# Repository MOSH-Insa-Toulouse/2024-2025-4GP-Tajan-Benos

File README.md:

# 2024-2025-4GP-Tajan-Benos

## SOMMAIRE
*** 
  - [I. Description Projet Graphite](#description-projet-graphite)
  - [II. Livrables](#livrables)
  - [III. Matériel nécessaire](#matériel-nécessaire)
  - [IV. Electronique Analogique sous LTSpice](#electronique-analogique-sous-ltspice)
  - [V. Création du PCB sous KiCad](#creation-du-pcb-sous-kicad)
  - [VI. Réalisation du shield](#réalisation-du-shield)
  - [VII. Code Arduino](#code-arduino)
  - [VIII. Application Android](#application-android)
  - [IX. Banc de test](#banc-de-test)
  - [X. Datasheet](#datasheet)
  - [XI. Conclusion](#conclusion)

*** 

## Description Projet Graphite

&nbsp;&nbsp;&nbsp;&nbsp;&nbsp;&nbsp; Dans le cadre de l’UE "Du capteur au banc de test" en 4e année de Génie Physique à l’INSA Toulouse, nous avons développé un capteur de contrainte basé sur une technologie low-tech. Ce capteur utilise du graphite déposé sur une feuille de papier à l’aide d’un crayon. Lorsqu’on applique une déformation au papier, la structure du graphite change, ce qui modifie ses propriétés électriques, comme la résistance. Ce capteur low-tech fonctionne grâce à la variation des connexions conductrices entre les nano-particules de graphite. Le transport des électrons se fait par effet tunnel entre les particules. Lorsqu'une déformation est appliquée, la distance entre les atomes varie. En extension, certains chemins de conduction sont interrompus, augmentant la résistance. En compression, la distance diminue, créant de nouveaux chemins et réduisant la résistance. La jauge de contrainte mesure ces variations de résistance pour déterminer la déformation et la contrainte appliquées. \
&nbsp;&nbsp;&nbsp;&nbsp;&nbsp;&nbsp; Le projet a consisté à développer un système complet autour de ce capteur : modélisation d'électronique analogique, création d’un circuit imprimé (PCB), programmation avec Arduino, ajout d’une interface utilisateur (écran OLED, encodeur, etc.) et communication sans fil via Bluetooth pour une application mobile. Un banc de test a été réalisé pour évaluer les performances du capteur à l'aide d'un banc de mesure réalisé en 3D. L’ensemble du travail a abouti à la rédaction d’une datasheet, décrivant les caractéristiques du capteur. Enfin, le projet visait à repondre à la question "Ce capteur est-il industrialisable ?", en comparaison avec les capteurs commerciaux déjà présents sur le marché.

## Livrables

  - Shield PCB compatible avec Arduino UNO, intégrant un capteur graphite, un amplificateur transimpédance, un module Bluetooth, un écran OLED, un flex sensor, un potentiomètre digital et un encodeur rotatoire
  - Code Arduino assurant la lecture du capteur, l’affichage des données, la communication Bluetooth et l’interaction avec les composants
  - Application Android réalisée sous MIT App Inventor pour visualiser les mesures transmises par Bluetooth
  - Graphes caractéristiques de la variation de résistance du capteur graphène et du flex sensor, pour montrer les résultats obtenus sur le banc de test
  - Datasheet du capteur de contrainte, présentant ses principales caractéristiques et résultats expérimentaux

## Matériel nécessaire

  - 1 carte Arduino Uno
  - 2 Résistances de 100kΩ
  - 1 Résistance de 1kΩ
  - 1 Potentiomètre digital MCP-41050
  - 2 Condensateurs 100nF
  - 1 Condensateur 1µF
  - 1 Amplificateur LTC1050
  - 1 Écran OLED01
  - 1 Module Bluetooth HC-05
  - 1 Encodeur rotatoire 

## Electronique Analogique sous LTSpice

Notre capteur en graphite présente une résistance de l’ordre du gigaohm, ce qui génère un courant de quelques pico- à nanoampères sous une tension de 5 V. Pour rendre ce signal exploitable par l’ADC d’une Arduino UNO, nous avons conçu un amplificateur transimpédance autour de l’AOP LTC1050, il a une très faible dérive et un excellent décalage d’offset. Après avoir modélisé le capteur et le montage sous LTspice pour de déterminer la meilleure valeur de la résistance de rétroaction, nous avons ajouté trois étages de filtrage afin d'améliorer la qualité du signal :  
   1- Filtre passe-bas à 16 Hz (R1–C1) pour éliminer les hautes fréquences parasites,  
   2- Filtre passe-bas à 1,6 Hz (R3–C4) pour atténuer le bruit secteur à 50 Hz,  
   3- Filtre passe-bas à 1,6 kHz (R6–C2) pour supprimer les interférences liées à l’ADC.  

Ce circuit convertit ainsi le faible courant issu du capteur en une tension propre, directement lisible et traitable par la carte Arduino.

<p align="center">

<br>
<i>Circuit amplificateur transimpédance</i>
</p>

## Création du PCB sous KiCad

Lors de la phase de conception du shield, nous avons d’abord repris le gabarit d’une carte Arduino UNO dans KiCad (version 8.0) pour garantir une compatibilité mécanique et électrique. Après avoir listé tous les éléments dont nous avions besoin, nous avons créé dans KiCad, les symboles et empreintes manquants en respectant leurs dimensions et l’écartement des broches. Voici le schéma électrique de l'ensemble de notre montage :

<p align="center">

<br>
<i>Circuit électronique</i>
</p>

Une fois notre bibliothèque faite, nous avons assemblé le schéma électrique complet : chaque composant est relié selon le fonctionnement prévu. Cette étape nous a permis de vérifier que l’ensemble des composants tenait bien sur la zone réservée au Shield. En passant à la vue PCB, nous avons effectué le routage des pistes dans le but d'une organisation optimale puis ajouté un plan de masse pour relier les pistes au GND. 
Voici notre PCB :

<p align="center">

<br>
<i>PCB</i>
</p>

Le résultat est un circuit imprimé prêt à être fabriqué et à recevoir chaque composant sur le shield Arduino UNO.

## Réalisation du Shield

Nous avons commencé par l’édition du masque de gravure de notre circuit imprimé (PCB) à l’aide du logiciel KiCad. Ensuite, nous avons procédé à l’insolation UV d’une plaquette d’époxy recouverte d’une fine couche de cuivre et de résine photosensible. La plaquette a ensuite été immergée dans un révélateur chimique, ce qui permet d’éliminer la résine non exposée aux UV. Il faut ensuite plonger la plaquette dans du perchlorure de fer pour graver les pistes du circuit en dissolvant le cuivre non protégé. Enfin, il faut un nettoyage à l’acétone pour retirer les résidus de résine restants sur la plaquette. A la fin de ce travail, nous avions notre circuit imprimé avec toutes les pistes tracées. 
Une fois le PCB réalisé, nous n'avions plus qu'à le percer et y souder tous nos composants. Voici notre PCB final :

<p align="center">

<br>
<i>Notre PCB</i>
</p>

## Code Arduino 

Ce projet a été piloté par un [programme Arduino](Code%20Arduino). Pour utiliser les fonctions spéciales à tous les composants, nous avons installé les librairies Adafruit_SSD1306.h , SPI.h , et SoftwareSerial.h.

Le programme permet d'initialiser et de paramétrer nos composants pour le bon fonctionnement du circuit. Une fois la carte mise sous tension, l'écran OLED affiche 4 possibilités sélectionnables grâce à l'encodeur rotatoire : 
- "Calib Potar" permettant de définir la valeur de la résistance du potentiomètre (notée R2 dans notre montage et notre code)
- "FlexSensor" pour réaliser une mesure momentanée de résistence du flex sensor
- "Capteur Graph" dans le but d'afficher la mesure de résistance sur le capteur graphène
- "Bluetooth" afin d'envoyer des mesures toutes les 2 secondes à l'application Androïd, permettant de modifier la courbure du capteur graphène et d'en remarquer la variation de résistance

<p align="center">

<br>
<i>Menu initial sur l'écran OLED</i>
</p>

Chaque possibilité est piloté par des fonctions indépendantes les unes des autres.

## Application Android

Nous avons conçu une application Android en utilisant la plateforme MIT App Inventor. Cette application permet de recevoir les données de la carte Arduino via une connexion Bluetooth en utilisant le module HC-05 qui se trouve sur notre shield. Après la connexion bluetooth, l'application nous donne en temps réel la valeur de la résistance du capteur graphite et trace sa courbe en fonction du temps sur un graphique.

<p align="center">

<br>
<i>Interface Application</i>
</p>
<p align="center">

<br>
<i>Schéma block</i>
</p>

## Banc de test

Après avoir réalisé le montage électrique complet, ainsi que les parties softwares adéquates, il était nécessaire de tester notre capteur ainsi que le capteur commercial pour pouvoir les comparer. 

Pour cela, nous avons utilisé le banc de test ci-dessous, constitué de 6 cylindres différents dont les diamètres D font 14,8 mm ; 19,8 mm ; 24,8 mm ; 29,8 mm ; 34,8 mm ; 39,8 mm.

<p align="center">

<br>
<i>Banc de test utilisé</i>
</p>

Pour toutes les mesures, nous avons assigné une valeur de 10 kΩ à la résistance du potentiomètre digital. En ce qui concerne le capteur graphène, nous déposions le graphite issu des crayons 6B, 3B, et B. Nous n'avons pas réussi à obtenir des valeurs convenables avec des crayons plus durs. 

Le principe du test est de poser le capteur sur le cylindre et de le tordre selon la courbure du cylindre. Une fois le capteur bien posé, nous relevons la valeur de la résistance. 

Pour nos calculs, les valeurs qui nous intéressent sont la variation relative de résitance ()
en fonction de la déformation (). 

Voici les courbes caractéristiques du capteur graphène, en tension et en compression : 

<p align="center">

<br>
<i>Caractéristique du Capteur Graphène en tension</i>
</p>

<p align="center">

<br>
<i>Caractéristique du Capteur Graphène en compression</i>
</p>

Et ci-dessous la caractéristique du flex sensor en tension : 

<p align="center">

<br>
<i>Caractéristique du flex sensor en tension</i>
</p>

Nous remarquons que la résistance évolue lorsque le capteur graphite est soumis à une déformation. En tension, la résistance augmente, tandis qu'en compression, elle diminue. Ce phénomène s'explique par le rapprochement des atomes lors de la compression, facilitant ainsi le passage du courant. Lors de la tension, les atomes s'éloignent, le courant a alors plus de mal pour passer. Les résultats montrent aussi que le type de crayon utilisé influence les valeurs de résistance mesurées. 

La capacité de déformation en compression du capteur graphène n'est pas très fiable selon nos résulats. Le modèle linéaire attendu s'éloigne de la caractéristique sur les grosses déformations. Ceci peut être en partie dû au frottement du graphite sur le banc de test, qui peut perturber l'agencement des atomes et ainsi les mesures réalisées. 

Ces résultats expérimentaux permettent de conclure que le capteur commercial est globalement plus sensible à la déformation que les capteurs en graphite, même si cette dernière est acceptable. De plus, il possède une certaine robustesse contrairement aux capteurs en papier : ceux-ci sont fragiles et n'importe quel contact peut altérer le gtaphite déposé. Le nombre d'utilisation est aussi limité, entre 1 et 3 séries de tests pour la plupart. Au-delà, les variations de résistance étaient très aléatoires et parfois inexistantes. Il était également nécessaire de déposer une grande quantité de graphite sur le papier pour pouvoir mesurer une résistance, notamment avec des crayons bien gras. 

## Datasheet

La datasheet de notre capteur est disponible [ici](Datasheet).

## Conclusion

Grâce à la série d'étapes amenant aux tests réalisés sur les deux capteurs, nous pouvons répondre à la question, à savoir si le capteur graphène est industrialisable ou non. 

Comme mentionnés dans la partie [IX. Banc de test](#banc-de-test), les résultats montrent que le capteur commercial possède plusieurs avantages par rapport au capteur graphène. Il est plus fiable, plus durable, et moins contraignant, ce qui nous amène à être réticents à l'idée de commercialiser notre capteur. Toutefois, sa sensibilité est plus qu'acceptable, et il est capable de mesurer en compression. Pour une utilisation unique et rapide, il reste une belle option. Si nous améliorions sa capacité de compression (en protégeant le graphite par un gel par exemple), il deviendrait une solution de choix. Mais cette solution est avant tout low tech, il faudrait donc rester acessible. 

Ce projet fût très enrichissant, il nous a permis de concevoir la partie software et hardware d'un capteur, tout en le testant et réalisant une datasheet. Les différentes étapes nous ont fait acquérir de nouvelles connaissances et compétances que nous retrouverons probablement dans notre future carrière d'ingénieur physicien. Nous remercions nos professeurs pour nous avoir proposé ce projet et accompagné tout au long de celui-ci. 

Vous pouvez nous contacter si vous avez la moindre question :
- Vicky BENOS : benos@insa-toulouse.fr
- Samuel TAJAN : stajan@insa-toulouse.fr

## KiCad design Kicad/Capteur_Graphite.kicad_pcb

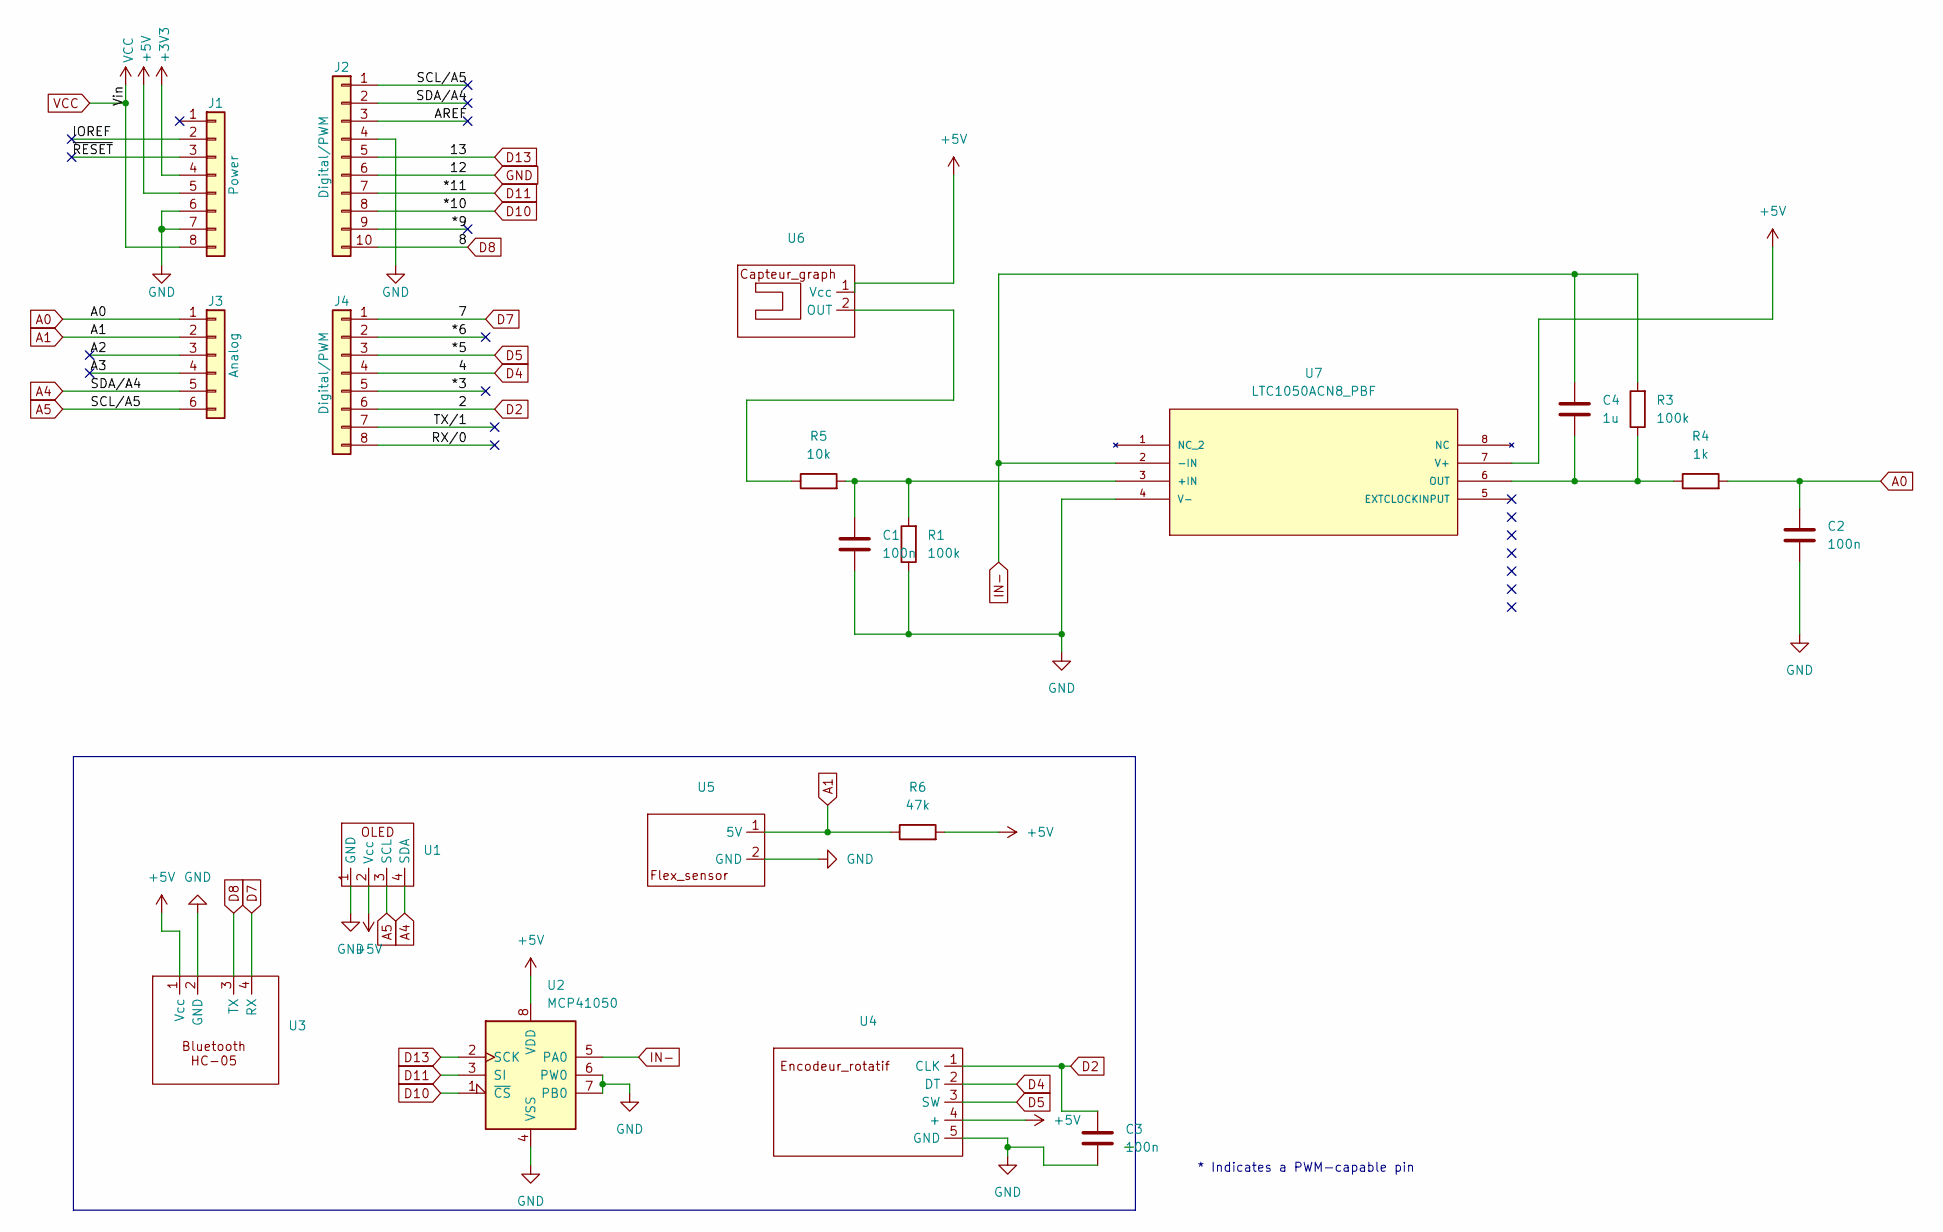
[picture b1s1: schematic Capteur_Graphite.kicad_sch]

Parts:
C1, C2, C3: 100n; C_Disc_D3.8mm_W2.6mm_P2.50mm
C4: 1u; C_Disc_D3.8mm_W2.6mm_P2.50mm
J1: Power; PinSocket_1x08_P2.54mm_Vertical
J2: Digital/PWM; PinSocket_1x10_P2.54mm_Vertical
J3: Analog; PinSocket_1x06_P2.54mm_Vertical
J4: Digital/PWM; PinSocket_1x08_P2.54mm_Vertical
R1, R3: 100k; R_Axial_DIN0204_L3.6mm_D1.6mm_P7.62mm_Horizontal
R4: 1k; R_Axial_DIN0204_L3.6mm_D1.6mm_P7.62mm_Horizontal
R5: 10k; R_Axial_DIN0204_L3.6mm_D1.6mm_P7.62mm_Horizontal
R6: 47k; R_Axial_DIN0204_L3.6mm_D1.6mm_P7.62mm_Horizontal
U1: OLED
U2: MCP41050
U3: BT
U4: Encodeur_rotatif
U5: Flex_sensor
U6: Capt_grap
U7: LTC1050ACN8_PBF; Ampli; MANUFACTURER_PART_NUMBER ltc1050acn8

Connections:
+3V3: J1.4
+5V: J1.5, R6.2, U1.2 (Vcc), U2.8 (VDD), U3.1 (Vcc), U4.4 (+), U6.1 (Vcc), U7.7 (V+)
/*3: J4.5
/*6: J4.2
/*9: J2.9
/A2: J3.3
/A3: J3.4
/AREF: J2.3
/IOREF: J1.2
/RX/0: J4.8
/TX/1: J4.7
/~RESET: J1.3
A0: C2.1, J3.1, R4.2
A1: J3.2, R6.1, U5.1 (5V)
A4: J2.2, J3.5, U1.4 (SDA)
A5: J2.1, J3.6, U1.3 (SCL)
D2: C3.1, J4.6, U4.1 (CLK)
D4: J4.4, U4.2 (DT)
D5: J4.3, U4.3 (SW)
D7: J4.1, U3.4 (RX)
D8: J2.10, U3.3 (TX)
D10: J2.8, U2.1 (~CS)
D11: J2.7, U2.3 (SI)
D13: J2.5, U2.2 (SCK)
GND: C1.2, C2.2, C3.2, J1.6, J1.7, J2.4, J2.6, R1.1, U1.1 (GND), U2.4 (VSS), U2.6 (PW0), U2.7 (PB0), U3.2 (GND), U4.5 (GND), U5.2 (GND), U7.4 (V-)
IN-: C4.1, R3.2, U2.5 (PA0), U7.2 (-IN)
unnamed: R5.1, U6.2 (OUT)
unnamed: C1.1, R1.2, R5.2, U7.3 (+IN)
unnamed: C4.2, R3.1, R4.1, U7.6 (OUT)
VCC: J1.8

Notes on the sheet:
* Indicates a PWM-capable pin

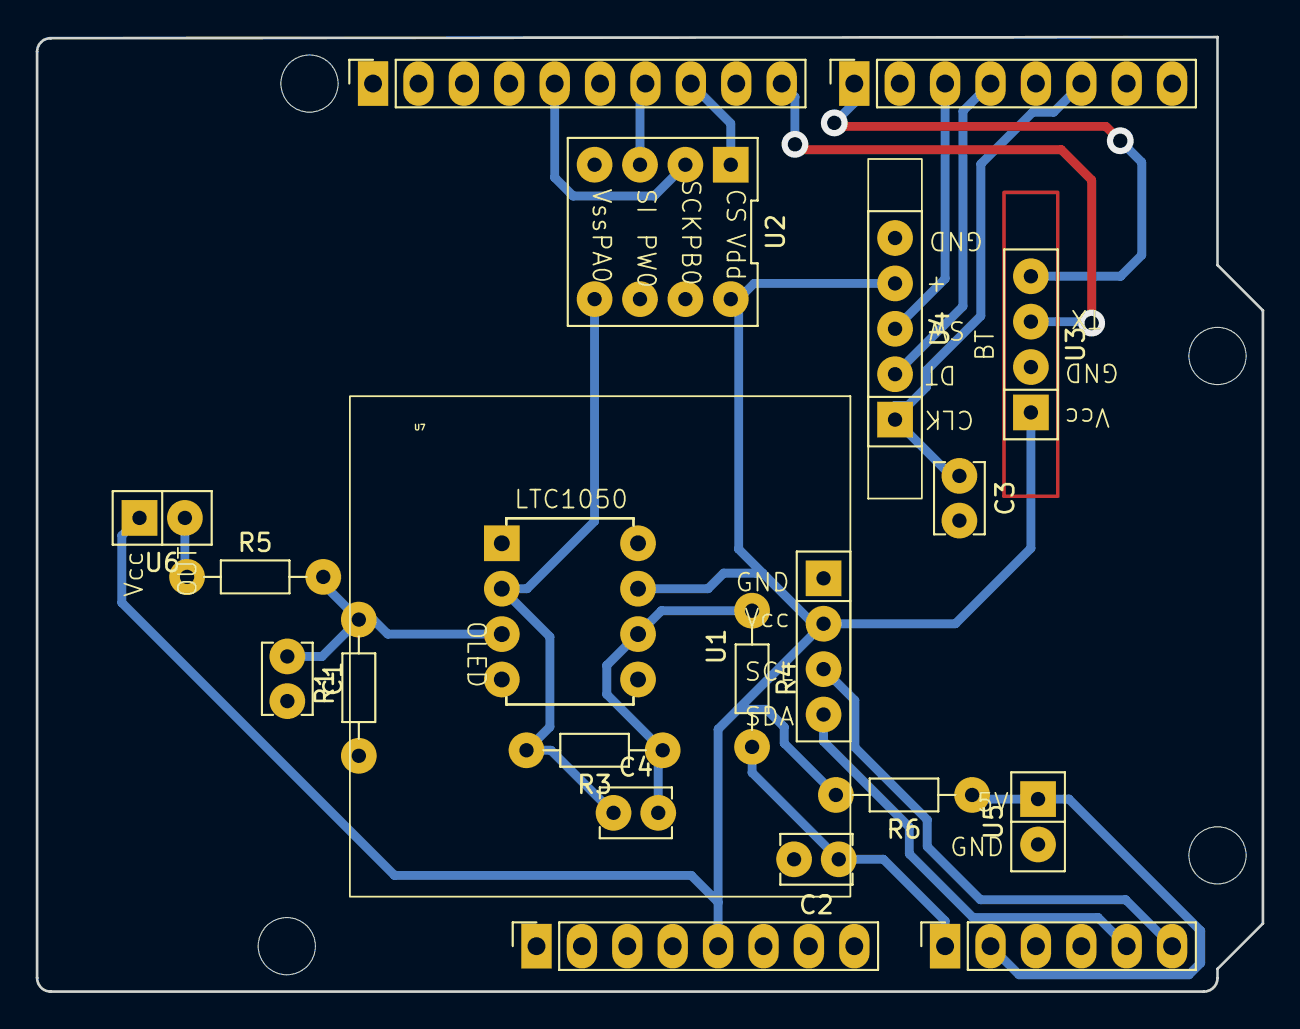
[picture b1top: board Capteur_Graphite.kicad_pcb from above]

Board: 2 copper layers, 68.6 x 53.4 mm, 24 parts (0 on the bottom side), 18 nets.

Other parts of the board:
MH1, MH2, MH3, MH4: MountingHole_3.2mm

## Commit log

2025-03-16 create_kicad_project_16/03
2025-04-23 Create Empreinte
2025-04-23 Create fdv
2025-04-23 Create frev
2025-04-23 Create vfvf
2025-04-23 Create frv
2025-05-29 Ajout du code final
2025-05-29 Create kicad
2025-05-29 Create datasheet
2025-05-29 Create dcsd
2025-05-29 Create cjcnjsd

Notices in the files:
parts and their libraries:
COPYRIGHT: Copyright C 2016 Accelerated Designs. All rights reserved
